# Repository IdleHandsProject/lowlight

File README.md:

# LowLight
No power button, several year lasting, low power flashlight.

This is currently just a copy pasta and merge of...

https://github.com/tedyapo/tritiled

and...

https://github.com/hexagon5un/everled

That will change soon.

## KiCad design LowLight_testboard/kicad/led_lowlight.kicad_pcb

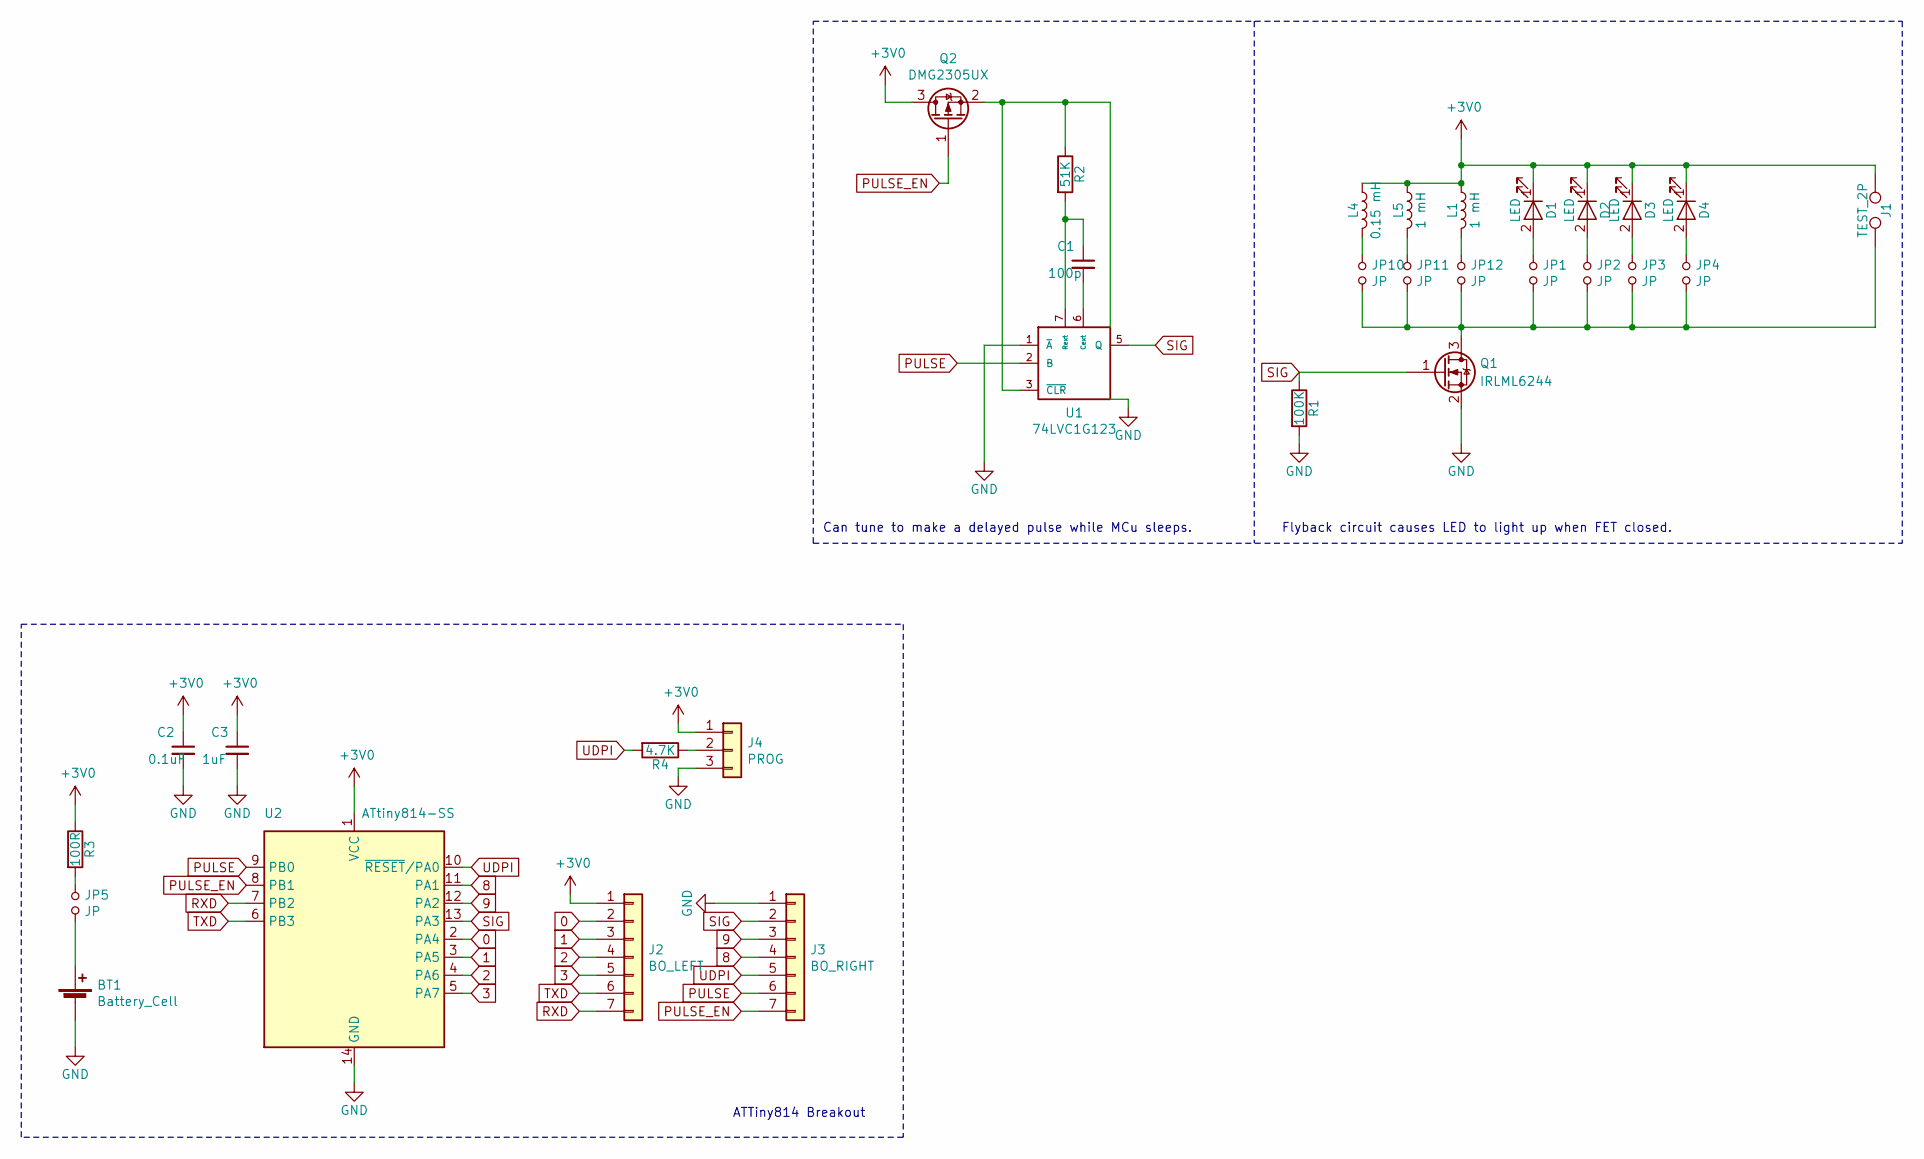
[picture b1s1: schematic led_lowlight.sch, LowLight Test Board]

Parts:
BT1: Battery_Cell; BatteryHolder_Keystone_1058_1x2032; Digikey Part No. 36-1058CT-ND
C1: 100p; C_0805_2012Metric; Digikey Part No. 399-1122-1-ND
C2: 0.1uF; C_0805_2012Metric; Digikey Part No. 1276-1286-1-ND
C3: 1uF; C_0805_2012Metric; Digikey Part No. 1276-3010-1-ND
D1: LED; LED_1W_3W_R8; Digikey Part No. 516-2565-ND
D2: LED; LED_1210_3225Metric
D3: LED; LED_Cree-XP-G; Digikey Part No. 475-3450-1-ND
D4: LED; LED_Cree-XP-G; Digikey Part No. XPEBGR-L1-0000-00F02CT-ND
J1: TEST_2P; PinHeader_1x02_P2.54mm_Vertical
J2: BO_LEFT; PinHeader_1x07_P2.54mm_Vertical; Digikey Part No. S7040-ND
J3: BO_RIGHT; PinHeader_1x07_P2.54mm_Vertical; Digikey Part No. S7040-ND
J4: PROG; PinHeader_1x03_P2.54mm_Vertical
JP1, JP2, JP3, JP4, JP5, JP10, JP11, JP12: JP; PinHeader_1x02_P2.54mm_Vertical
L1: 1 mH; L_Bourns-SRN6028; Digikey Part No. SRR6028-102YCT-ND
L4: 0.15 mH; L_1210_3225Metric
L5: 1 mH; L_Bourns-SRN6028; Digikey Part No. 587-2041-6-ND
Q1: IRLML6244; SOT-23; Digikey Part No. IRLML6244TRPBFCT-ND
Q2: DMG2305UX; SOT-23; Digikey Part No. DMG2305UX-7DICT-ND
R1: 100K; R_0805_2012Metric; Digikey Part No. 311-100KARCT-ND
R2: 51K; R_0805_2012Metric; Digikey Part No. 311-51KARCT-ND
R3: 100R; R_0805_2012Metric; Digikey Part No. 311-100ARCT-ND
R4: 4.7K; R_0805_2012Metric; Digikey Part No. 311-4.7KARCT-ND
U1: 74LVC1G123; VSSOP-8_2.4x2.1mm_P0.5mm; Digikey Part No. 1727-2067-1-ND
U2: ATtiny814-SS; SOIC-14_3.9x8.7mm_P1.27mm; Digikey Part No. ATTINY814-SSFRTR-ND

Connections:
0: J2.2, U2.2 (PA4)
1: J2.3, U2.3 (PA5)
2: J2.4, U2.4 (PA6)
3: J2.5, U2.5 (PA7)
8: J3.4, U2.11 (PA1)
9: J3.3, U2.12 (PA2)
+3V0: C2.1, C3.1, D1.1 (K), D2.1 (K), D3.1 (K), D4.1 (K), J1.1, J2.1, J4.1, L1.1, L4.1, L5.1, Q2.3 (D), R3.1, U2.1 (VCC)
GND: BT1.2 (-), C2.2, C3.2, J3.1, J4.3, Q1.2 (S), R1.2, U1.1 (~A), U1.4 (GND), U2.14 (GND)
unnamed: BT1.1 (+), JP5.2
unnamed: C1.1, R2.2, U1.7 (Rext)
unnamed: C1.2, U1.6 (Cext)
unnamed: D1.2 (A), JP1.1
unnamed: D2.2 (A), JP2.1
unnamed: D3.2 (A), JP3.1
unnamed: D4.2 (A), JP4.1
unnamed: J1.2, JP1.2, JP2.2, JP3.2, JP4.2, JP10.2, JP11.2, JP12.2, Q1.3 (D)
unnamed: J4.2, R4.1
unnamed: JP5.1, R3.2
unnamed: JP10.1, L4.2
unnamed: JP11.1, L5.2
unnamed: JP12.1, L1.2
PULSE: J3.6, U1.2 (B), U2.9 (PB0)
PULSE_EN: J3.7, Q2.1 (G), U2.8 (PB1)
RXD: J2.7, U2.7 (PB2)
SIG: J3.2, Q1.1 (G), R1.1, U1.5 (Q), U2.13 (PA3)
TXD: J2.6, U2.6 (PB3)
UDPI: J3.5, R4.2, U2.10 (~RESET~/PA0)
VCC: Q2.2 (S), R2.1, U1.3 (~CLR), U1.8 (VCC)

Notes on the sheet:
Can tune to make a delayed pulse while MCu sleeps.
Flyback circuit causes LED to light up when FET closed.
ATTiny814 Breakout

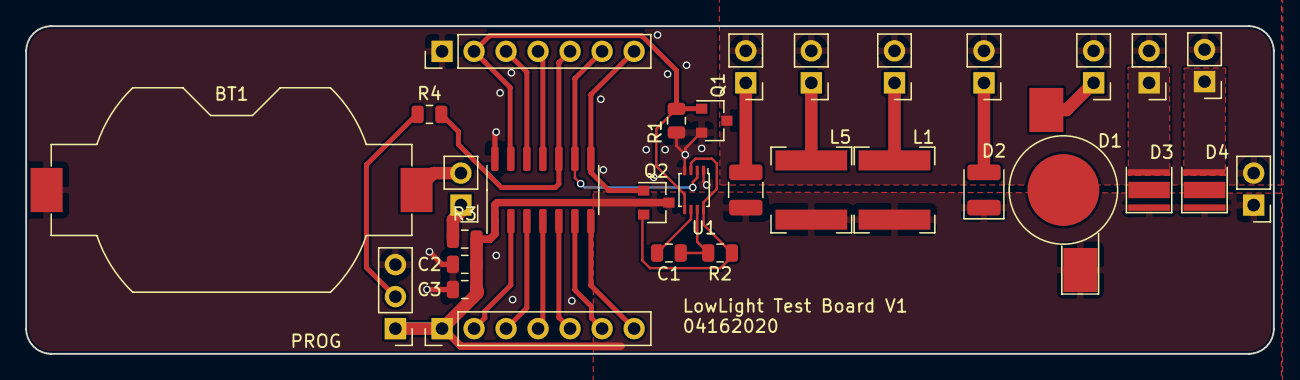
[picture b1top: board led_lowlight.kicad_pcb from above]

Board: 2 copper layers, 99.0 x 26.0 mm, 31 parts (0 on the bottom side), 28 nets.

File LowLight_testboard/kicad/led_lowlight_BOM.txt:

ref,value,footprint,Digikey Part No.,Mouser Part No.,Quantity
D3,LED,LED_SMD:LED_Cree-XP-G,475-3450-1-ND,,1
BT1,Battery_Cell,Battery:BatteryHolder_Keystone_1058_1x2032,36-1058CT-ND,,1
L5,1 mH,Inductor_SMD:L_Bourns-SRN6028,587-2041-6-ND,,1
R1,100K,Resistor_SMD:R_0805_2012Metric,311-100KARCT-ND,,1
U2,ATtiny814-SS,Package_SO:SOIC-14_3.9x8.7mm_P1.27mm,ATTINY814-SSFRTR-ND,,1
R3,100R,Resistor_SMD:R_0805_2012Metric,311-100ARCT-ND,,1
J2 J3,BO_LEFT,Connector_PinHeader_2.54mm:PinHeader_1x07_P2.54mm_Vertical,S7040-ND,,2
R2,51K,Resistor_SMD:R_0805_2012Metric,311-51KARCT-ND,,1
D4,LED,LED_SMD:LED_Cree-XP-G,XPEBGR-L1-0000-00F02CT-ND,,1
R4,4.7K,Resistor_SMD:R_0805_2012Metric,311-4.7KARCT-ND,,1
D1,LED,LED_SMD:LED_1W_3W_R8,516-2565-ND,,1
U1,74LVC1G123,Package_SO:VSSOP-8_2.4x2.1mm_P0.5mm,296-18758-1-ND,,1
L1,1 mH,Inductor_SMD:L_Bourns-SRN6028,SRR6028-102YCT-ND,,1
C3,1uF,Capacitor_SMD:C_0805_2012Metric,1276-3010-1-ND,,1
C2,0.1uF,Capacitor_SMD:C_0805_2012Metric,1276-1286-1-ND,,1
Q2,DMG2305UX,Package_TO_SOT_SMD:SOT-23,DMG2305UX-7DICT-ND,,1
C1,100p,Capacitor_SMD:C_0805_2012Metric,399-1122-1-ND,,1
Q1,IRLML6244,Package_TO_SOT_SMD:SOT-23,IRLML6244TRPBFCT-ND,,1

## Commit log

2020-04-16 first commit - test board
2020-04-16 added pdf schem
2020-04-16 added firmware for test board
